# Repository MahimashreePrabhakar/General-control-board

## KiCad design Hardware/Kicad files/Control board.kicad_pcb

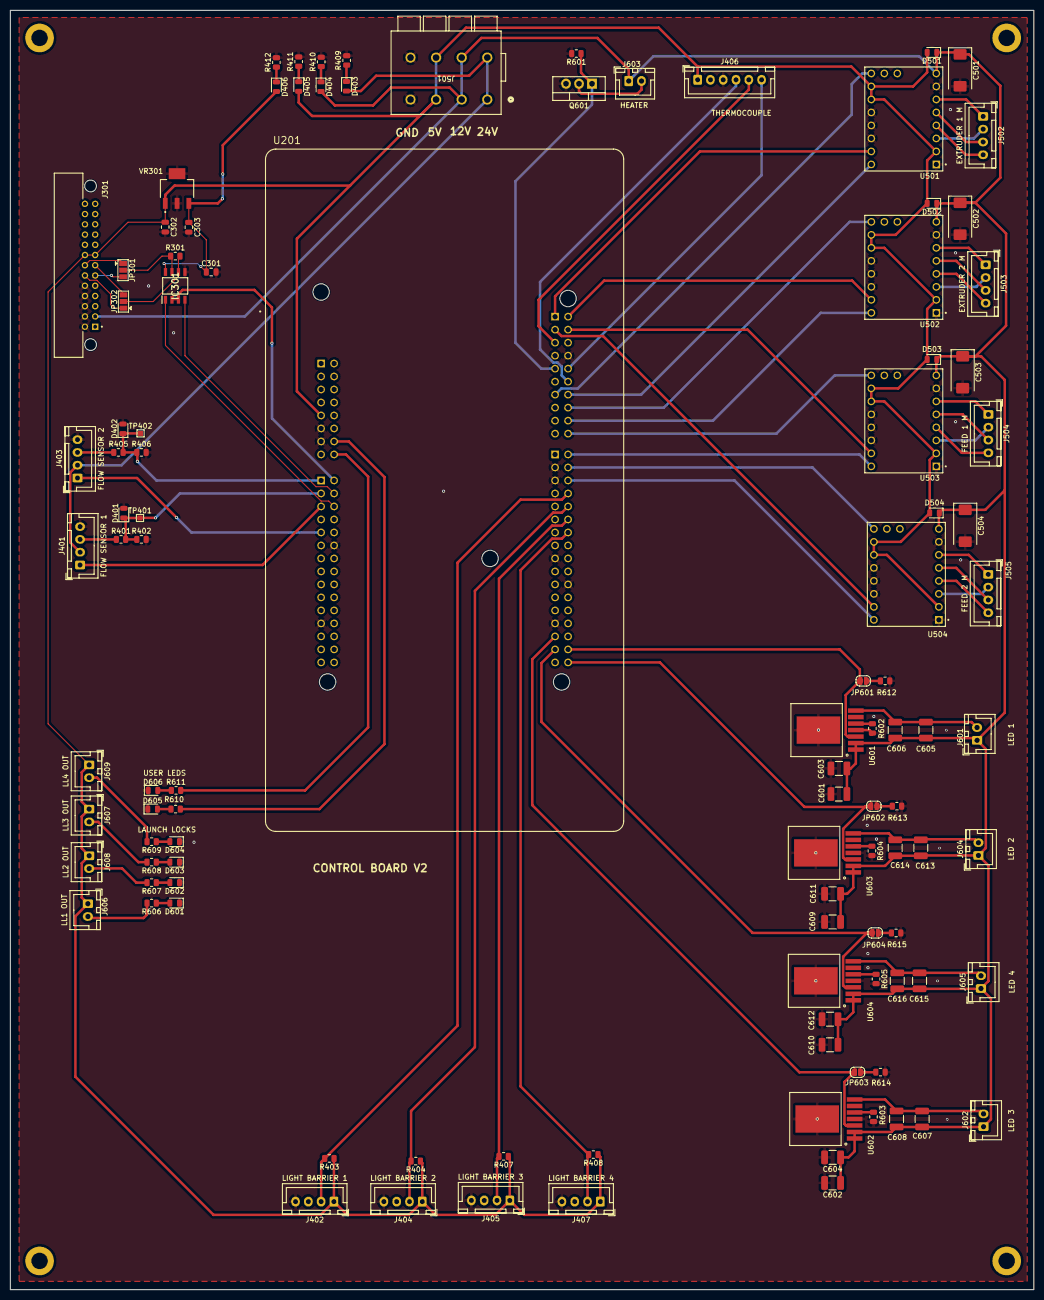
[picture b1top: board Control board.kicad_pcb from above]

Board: 2 copper layers, 200.0 x 250.0 mm, 113 parts (0 on the bottom side), 89 nets.

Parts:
C301: 10Nf; C_0805_2012Metric
C302: 0.47Uf; C_0805_2012Metric
C303: 33Uf; C_0805_2012Metric
C501, C502, C503, C504: TPSD107K010H0065; CP_EIA-7343-31_Kemet-D
C601, C602, C603, C604, C605, C606, C607, C608, C609, C610, C611, C612, C613, C614, C615, C616: 2.2uF 100V 1210; C_1210_3225Metric_Pad1.33x2.70mm_HandSolder
D401, D402, D501, D502, D503, D504: SD0805S040S0R5; D_0805_2012Metric
D403: RED; LED_0805_2012Metric
D404: BLUE; LED_0805_2012Metric
D405: GREEN; LED_0805_2012Metric
D406: YELLOW; LED_0805_2012Metric
D601, D602, D603, D604, D605, D606: LED; LED_0805_2012Metric
H301, H302, H303, H304: MountingHole; MountingHole_3.2mm_M3_DIN965_Pad
IC301: THVD1330DR; SOIC127P600X175-8N
J301: M80-5402642; HARWIN_M80-5402642
J401: FLOW SENSOR 1; JST_XH_B4B-XH-A_1x04_P2.50mm_Vertical
J402: LIGHT BARRIER 1; JST_XH_B4B-XH-A_1x04_P2.50mm_Vertical
J403: FLOW SENSOR 2; JST_XH_B4B-XH-A_1x04_P2.50mm_Vertical
J404: LIGHT BARRIER 2; JST_XH_B4B-XH-A_1x04_P2.50mm_Vertical
J405: LIGHT BARRIER 3; JST_XH_B4B-XH-A_1x04_P2.50mm_Vertical
J406: THERMOCOUPLE 1; JST_XH_B6B-XH-A_1x06_P2.50mm_Vertical
J407: LIGHT BARRIER 4; JST_XH_B4B-XH-A_1x04_P2.50mm_Vertical
J501: 2604-1104; CONN4_2604-1104_WAG
J502: EXTRUDER 1 M; JST_XH_B4B-XH-A_1x04_P2.50mm_Vertical
J503: EXTRUDER 2 M; JST_XH_B4B-XH-A_1x04_P2.50mm_Vertical
J504: FEED 1 M; JST_XH_B4B-XH-A_1x04_P2.50mm_Vertical
J505: FEED 2 M; JST_XH_B4B-XH-A_1x04_P2.50mm_Vertical
J601: LED 1; JST_XH_B2B-XH-A_1x02_P2.50mm_Vertical
J602: LED 3; JST_XH_B2B-XH-A_1x02_P2.50mm_Vertical
J603: HEATER; JST_XH_B2B-XH-A_1x02_P2.50mm_Vertical
J604: LED 2; JST_XH_B2B-XH-A_1x02_P2.50mm_Vertical
J605: LED 4; JST_XH_B2B-XH-A_1x02_P2.50mm_Vertical
J606: LL1 OUT; JST_XH_B2B-XH-A_1x02_P2.50mm_Vertical
J607: LL3 OUT; JST_XH_B2B-XH-A_1x02_P2.50mm_Vertical
J608: LL2 OUT; JST_XH_B2B-XH-A_1x02_P2.50mm_Vertical
J609: LL4 OUT; JST_XH_B2B-XH-A_1x02_P2.50mm_Vertical
JP301: SJ1_Open; SolderJumper-3_P1.3mm_Open_Pad1.0x1.5mm
JP302: SJ2_Open; SolderJumper-3_P1.3mm_Open_Pad1.0x1.5mm
JP601, JP602, JP603, JP604: PULL DOWN; SolderJumper-2_P1.3mm_Open_RoundedPad1.0x1.5mm
Q601: IRLB8721PBF; TO-220-3_Vertical
R301: 120R; R_0805_2012Metric
R401, R402, R405, R406: 10K; R_0805_2012Metric
R403, R404, R407, R408, R601: 47K; R_0805_2012Metric
R409, R411, R412: R; R_0805_2012Metric
R410: 860R; R_0805_2012Metric
R602, R603, R604, R605: 2.33K; R_0805_2012Metric
R606: 330 R; R_0805_2012Metric
R607, R608, R609, R610, R611: 330R; R_0805_2012Metric
R612, R613, R614, R615: 470R; R_0805_2012Metric
TP401, TP402: TestPoint; TestPoint_Pad_1.0x1.0mm
U201: NUCLEO-H753ZI; MODULE_NUCLEO-H753ZI
U501, U502, U503, U504: TMC2209_SILENTSTEPSTICK; MODULE_TMC2209_SILENTSTEPSTICK
U601, U602, U603, U604: MAGIC-LDHM_172946001
VR301: LM3940IMP-3.3_NOPB; VREG_LM3940IMP-3.3_NOPB

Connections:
5V: C302.1, D405.2 (A), D501.2 (A), D502.2 (A), D503.2 (A), D504.2 (A), J301.8, J301.21, J402.1, J404.1, J405.1, J406.1, J407.1, J501.5 (3_1), J501.6 (3_2), J606.1, J607.1, J608.1, J609.1, R403.1, R404.1, R407.1, R408.1, U201.CN8_9 (5V_CN8), U501.2 (VIO), U501.14 (MS2), U501.15 (MS1), U502.2 (VIO), U502.14 (MS2), U502.15 (MS1), U503.2 (VIO), U503.14 (MS2), U503.15 (MS1), U504.2 (VIO), U504.14 (MS2), U504.15 (MS1), VR301.1 (IN)
12V: C501.1, C502.1, C503.1, C504.1, C601.1, C602.1, C603.1, C604.1, C605.1, C606.1, C607.1, C608.1, C609.1, C610.1, C611.1, C612.1, C613.1, C614.1, C615.1, C616.1, D404.2 (A), D501.1 (K), D502.1 (K), D503.1 (K), D504.1 (K), J301.2, J501.3 (2_1), J501.4 (2_2), J601.1, J602.1, J603.1, J604.1, J605.1, U501.8 (VM), U502.8 (VM), U503.8 (VM), U504.8 (VM), U601.1, U601.2, U602.1, U602.2, U603.1, U603.2, U604.1, U604.2
24V: D403.2 (A), J401.2, J403.2, J501.1 (1_1), J501.2 (1_2)
+3V3: C301.1, C303.1, D406.2 (A), IC301.8 (VCC), VR301.3 (OUT)
D1 IN: R610.2, U201.CN8_14 (D49/IO)
D2 IN: R611.2, U201.CN8_16 (D50/IO)
DE: IC301.2 (~RE), IC301.3 (DE), U201.CN9_2 (D51/USART_B_SCLK)
F1_OUT: D401.1 (K), R401.2, R402.1, TP401.1, U201.CN9_3 (A1/ADC123_INP10)
F2_OUT: D402.1 (K), R405.2, R406.1, TP402.1, U201.CN9_1 (A0/ADC12_INP15)
GND: C301.2, C302.2, C303.2, C501.2, C502.2, C503.2, C504.2, C601.2, C602.2, C603.2, C604.2, C609.2, C610.2, C611.2, C612.2, D401.2 (A), D402.2 (A), D601.1 (K), D602.1 (K), D603.1 (K), D604.1 (K), D605.1 (K), D606.1 (K), IC301.5 (GND), J301.14, J301.15, J301.16, J301.17, J301.18, J401.4, J402.4, J403.4, J404.4, J405.4, J406.3, J407.4, J501.7 (4_1), J501.8 (4_2), Q601.3 (S), R402.2, R406.2, R409.2, R410.2, R411.2, R412.2, R601.2, R602.2, R603.2, R604.2, R605.2, R612.2, R613.2, R614.2, R615.2, U201.CN7_8 (GND_CN7), U201.CN8_11 (GND_CN8), U201.CN8_13 (GND_CN8), U201.CN9_12 (GND_CN9), U201.CN9_23 (GND_CN9), U201.CN10_3 (AGND_CN10), U201.CN10_5 (GND_CN10), U201.CN10_17 (GND_CN10), U201.CN10_22 (GND_CN10), U201.CN10_27 (GND_CN10), U501.1 (GND), U501.7 (GND), U501.11 (PDN), U501.12 (UART), U501.13 (SPRD), U502.1 (GND), U502.7 (GND), U502.11 (PDN), U502.12 (UART), U502.13 (SPRD), U503.1 (GND), U503.7 (GND), U503.11 (PDN), U503.12 (UART), U503.13 (SPRD), U504.1 (GND), U504.7 (GND), U504.11 (PDN), U504.12 (UART), U504.13 (SPRD), U601.4, U601.EP, U602.4, U602.EP, U603.4, U603.EP, U604.4, U604.EP, VR301.2 (GND_2), VR301.4 (GND_4)
HEATER IN: Q601.1 (G), R601.1, U201.CN7_9 (D20/I2S_B_WS)
L1_PWM: JP601.2 (B), U201.CN10_32 (D36/TIMER_C_PWM2), U601.3
L2_PWM: JP602.2 (B), U201.CN10_34 (D35/TIMER_C_PWM3), U603.3
L3_PWM: JP603.2 (B), U201.CN10_29 (D32/TIMER_C_PWM1), U602.3
L4_PWM: JP604.2 (B), U201.CN10_31 (D33/TIMER_D_PWM1), U604.3
LB1_OUT: J402.2, R403.2, U201.CN10_8 (D4/IO)
LB2_OUT: J404.2, R404.2, U201.CN10_10 (D3/TIMER_A_PWM3)
LB3_OUT: J405.2, R407.2, U201.CN10_12 (D2/IO)
LB4_OUT: J407.2, R408.2, U201.CN10_14 (D1/USART_A_TX)
LL1 IN: J606.2, R606.2
LL2 IN: J608.2, R607.2
LL3 IN: J607.2, R608.2
LL4 IN: J609.2, R609.2
M1_DIR: U201.CN7_14 (D11/SPI_A_MOSI/TIM_E_PWM1), U501.9 (DIR)
M1_EN: U201.CN7_13 (D22/I2S_B_SD/SPI_B_MOSI), U501.16 (~EN)
M1_PWM: U201.CN7_1 (D16/I2S_A_MCK), U501.10 (STEP)
M2_DIR: U201.CN7_18 (D9/TIMER_B_PWM2), U502.9 (DIR)
M2_EN: U201.CN7_16 (D10/SPI_A_CS/TIM_B_PWM3), U502.16 (~EN)
M2_PWM: U201.CN7_2 (D15/I2C_A_SCL), U502.10 (STEP)
M3_DIR: U201.CN10_2 (D7/IO), U503.9 (DIR)
M3_EN: U201.CN7_20 (D8/IO), U503.16 (~EN)
M3_PWM: U201.CN7_4 (D14/I2C_A_SDA), U503.10 (STEP)
M4_DIR: U201.CN10_6 (D5/TIMER_A_PWM2), U504.9 (DIR)
M4_EN: U201.CN10_4 (D6/TIMER_A_PWM1), U504.16 (~EN)
M4_PWM: U201.CN7_3 (D17/I2S_A_SD), U504.10 (STEP)
unnamed: D403.1 (K), R409.1
unnamed: D404.1 (K), R410.1
unnamed: D405.1 (K), R411.1
unnamed: D406.1 (K), R412.1
unnamed: D601.2 (A), R606.1
unnamed: D602.2 (A), R607.1
unnamed: D603.2 (A), R608.1
unnamed: D604.2 (A), R609.1
unnamed: D605.2 (A), R610.1
unnamed: D606.2 (A), R611.1
unnamed: J401.3, R401.1
unnamed: J403.3, R405.1
unnamed: J502.1, U501.6 (M2B)
unnamed: J502.2, U501.3 (M1B)
unnamed: J502.3, U501.5 (M2A)
unnamed: J502.4, U501.4 (M1A)
unnamed: J503.1, U502.6 (M2B)
unnamed: J503.2, U502.3 (M1B)
unnamed: J503.3, U502.5 (M2A)
unnamed: J503.4, U502.4 (M1A)
unnamed: J504.1, U503.6 (M2B)
unnamed: J504.2, U503.3 (M1B)
unnamed: J504.3, U503.5 (M2A)
unnamed: J504.4, U503.4 (M1A)
unnamed: J505.1, U504.6 (M2B)
unnamed: J505.2, U504.3 (M1B)
unnamed: J505.3, U504.5 (M2A)
unnamed: J505.4, U504.4 (M1A)
unnamed: C605.2, C606.2, J601.2, U601.7
unnamed: C607.2, C608.2, J602.2, U602.7
unnamed: J603.2, Q601.2 (D)
unnamed: C613.2, C614.2, J604.2, U603.7
unnamed: C615.2, C616.2, J605.2, U604.7
unnamed: JP601.1 (A), R612.1
unnamed: JP602.1 (A), R613.1
unnamed: JP603.1 (A), R614.1
unnamed: JP604.1 (A), R615.1
unnamed: R602.1, U601.5
unnamed: R603.1, U602.5
unnamed: R604.1, U603.5
unnamed: R605.1, U604.5
RS485RX+: J301.20, JP301.1 (A)
RS485RX-: J301.19, JP302.1 (A)
RS485TX+: J301.6, JP301.3 (B)
RS485TX-: J301.7, JP302.3 (B)
RS485_A: IC301.7 (B), JP301.2 (C), R301.1
RS485_B: IC301.6 (A), JP302.2 (C), R301.2
RX: IC301.4 (D), U201.CN9_4 (D52/USART_B_RX)
TEMP 1 OUT: J401.1, U201.CN9_5 (A2/ADC12_INP13)
TEMP 2 OUT: J403.1, U201.CN9_9 (A4/ADC123_INP12/I2C1_SDA)
TH_CLK1: J406.6, U201.CN7_10 (D13/SPI_A_SCK)
TH_CS1: J406.5, U201.CN7_5 (D18/I2S_A_CK)
TH_DO/MISO1: J406.4, U201.CN7_12 (D12/SPI_A_MISO)
TX: IC301.1 (R), U201.CN9_6 (D53/USART_B_TX)

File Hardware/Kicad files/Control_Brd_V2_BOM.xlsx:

Comment | Designator | Footprint | JLCPCB Part #（optional）
TPSD107K010H0065 | C501,C502,C503,C504 | Capacitor_Tantalum_SMD:CP_EIA-7343-31_Kemet-D
2.2uF 100V 1210 | C601,C602,C603,C604,C605,C606,C607,C608,C609,C610,C611,C612,C613,C614,C615,C616 | Capacitor_SMD:C_1210_3225Metric_Pad1.33x2.70mm_HandSolder
SD0805S040S0R5 | D401,D402,D501,D502,D503,D504 | Diode_SMD:D_0805_2012Metric
LED | D601,D602,D603,D604,D605,D606 | LED_SMD:LED_0805_2012Metric
M80-5402642 | J301 | footprints:HARWIN_M80-5402642
FLOW SENSOR 1 | J401 | Connector_JST:JST_XH_B4B-XH-A_1x04_P2.50mm_Vertical
LIGHT BARRIER 1 | J402 | Connector_JST:JST_XH_B4B-XH-A_1x04_P2.50mm_Vertical
FLOW SENSOR 2 | J403 | Connector_JST:JST_XH_B4B-XH-A_1x04_P2.50mm_Vertical
LIGHT BARRIER 2 | J404 | Connector_JST:JST_XH_B4B-XH-A_1x04_P2.50mm_Vertical
LIGHT BARRIER 3 | J405 | Connector_JST:JST_XH_B4B-XH-A_1x04_P2.50mm_Vertical
THERMOCOUPLE 1 | J406 | Connector_JST:JST_XH_B6B-XH-A_1x06_P2.50mm_Vertical
LIGHT BARRIER 4 | J407 | Connector_JST:JST_XH_B4B-XH-A_1x04_P2.50mm_Vertical
2604-1104 | J501 | footprints:CONN4_2604-1104_WAG
EXTRUDER 1 M | J502 | Connector_JST:JST_XH_B4B-XH-A_1x04_P2.50mm_Vertical
EXTRUDER 2 M | J503 | Connector_JST:JST_XH_B4B-XH-A_1x04_P2.50mm_Vertical
FEED 1 M | J504 | Connector_JST:JST_XH_B4B-XH-A_1x04_P2.50mm_Vertical
FEED 2 M | J505 | Connector_JST:JST_XH_B4B-XH-A_1x04_P2.50mm_Vertical
LED 1 | J601 | Connector_JST:JST_XH_B2B-XH-A_1x02_P2.50mm_Vertical
LED 3 | J602 | Connector_JST:JST_XH_B2B-XH-A_1x02_P2.50mm_Vertical
HEATER | J603 | Connector_JST:JST_XH_B2B-XH-A_1x02_P2.50mm_Vertical
LED 2 | J604 | Connector_JST:JST_XH_B2B-XH-A_1x02_P2.50mm_Vertical
LED 4 | J605 | Connector_JST:JST_XH_B2B-XH-A_1x02_P2.50mm_Vertical
LL1 OUT | J606 | Connector_JST:JST_XH_B2B-XH-A_1x02_P2.50mm_Vertical
LL3 OUT | J607 | Connector_JST:JST_XH_B2B-XH-A_1x02_P2.50mm_Vertical
LL2 OUT | J608 | Connector_JST:JST_XH_B2B-XH-A_1x02_P2.50mm_Vertical
LL4 OUT | J609 | Connector_JST:JST_XH_B2B-XH-A_1x02_P2.50mm_Vertical
IRLB8721PBF | Q601 | Package_TO_SOT_THT:TO-220-3_Vertical
10K | R401,R402,R405,R406 | Resistor_SMD:R_0805_2012Metric
47K | R403,R404,R407,R408,R601 | Resistor_SMD:R_0805_2012Metric
2.33K | R602,R603,R604,R605 | Resistor_SMD:R_0805_2012Metric
330 R | R606 | Resistor_SMD:R_0805_2012Metric
330R | R607,R608,R609,R610,R611 | Resistor_SMD:R_0805_2012Metric
470R | R612,R613,R614,R615 | Resistor_SMD:R_0805_2012Metric
TestPoint | TP401,TP402 | TestPoint:TestPoint_Pad_1.0x1.0mm
NUCLEO-H753ZI | U201 | Nucleo-H753ZI:MODULE_NUCLEO-H753ZI
MAX485_MODULE_5V_LOGIC_TLL_TO_RS-485_CONVERTER | U301 | footprints:MODULE_MAX485_MODULE_5V_LOGIC_TLL_TO_RS-485_CONVERTER
TMC2209_SILENTSTEPSTICK | U501,U502,U503,U504 | footprints:MODULE_TMC2209_SILENTSTEPSTICK
MAGIC-LDHM_172946001 | U601,U602,U603,U604 | footprints:MAGIC-LDHM_172946001

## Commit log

2024-11-14 includes the modifications made
2024-11-14 Python interface file
2024-11-14 [feat] trial for Stm UART,PWM,GPIOs
2024-11-14 UART, PWM, GPIOs
